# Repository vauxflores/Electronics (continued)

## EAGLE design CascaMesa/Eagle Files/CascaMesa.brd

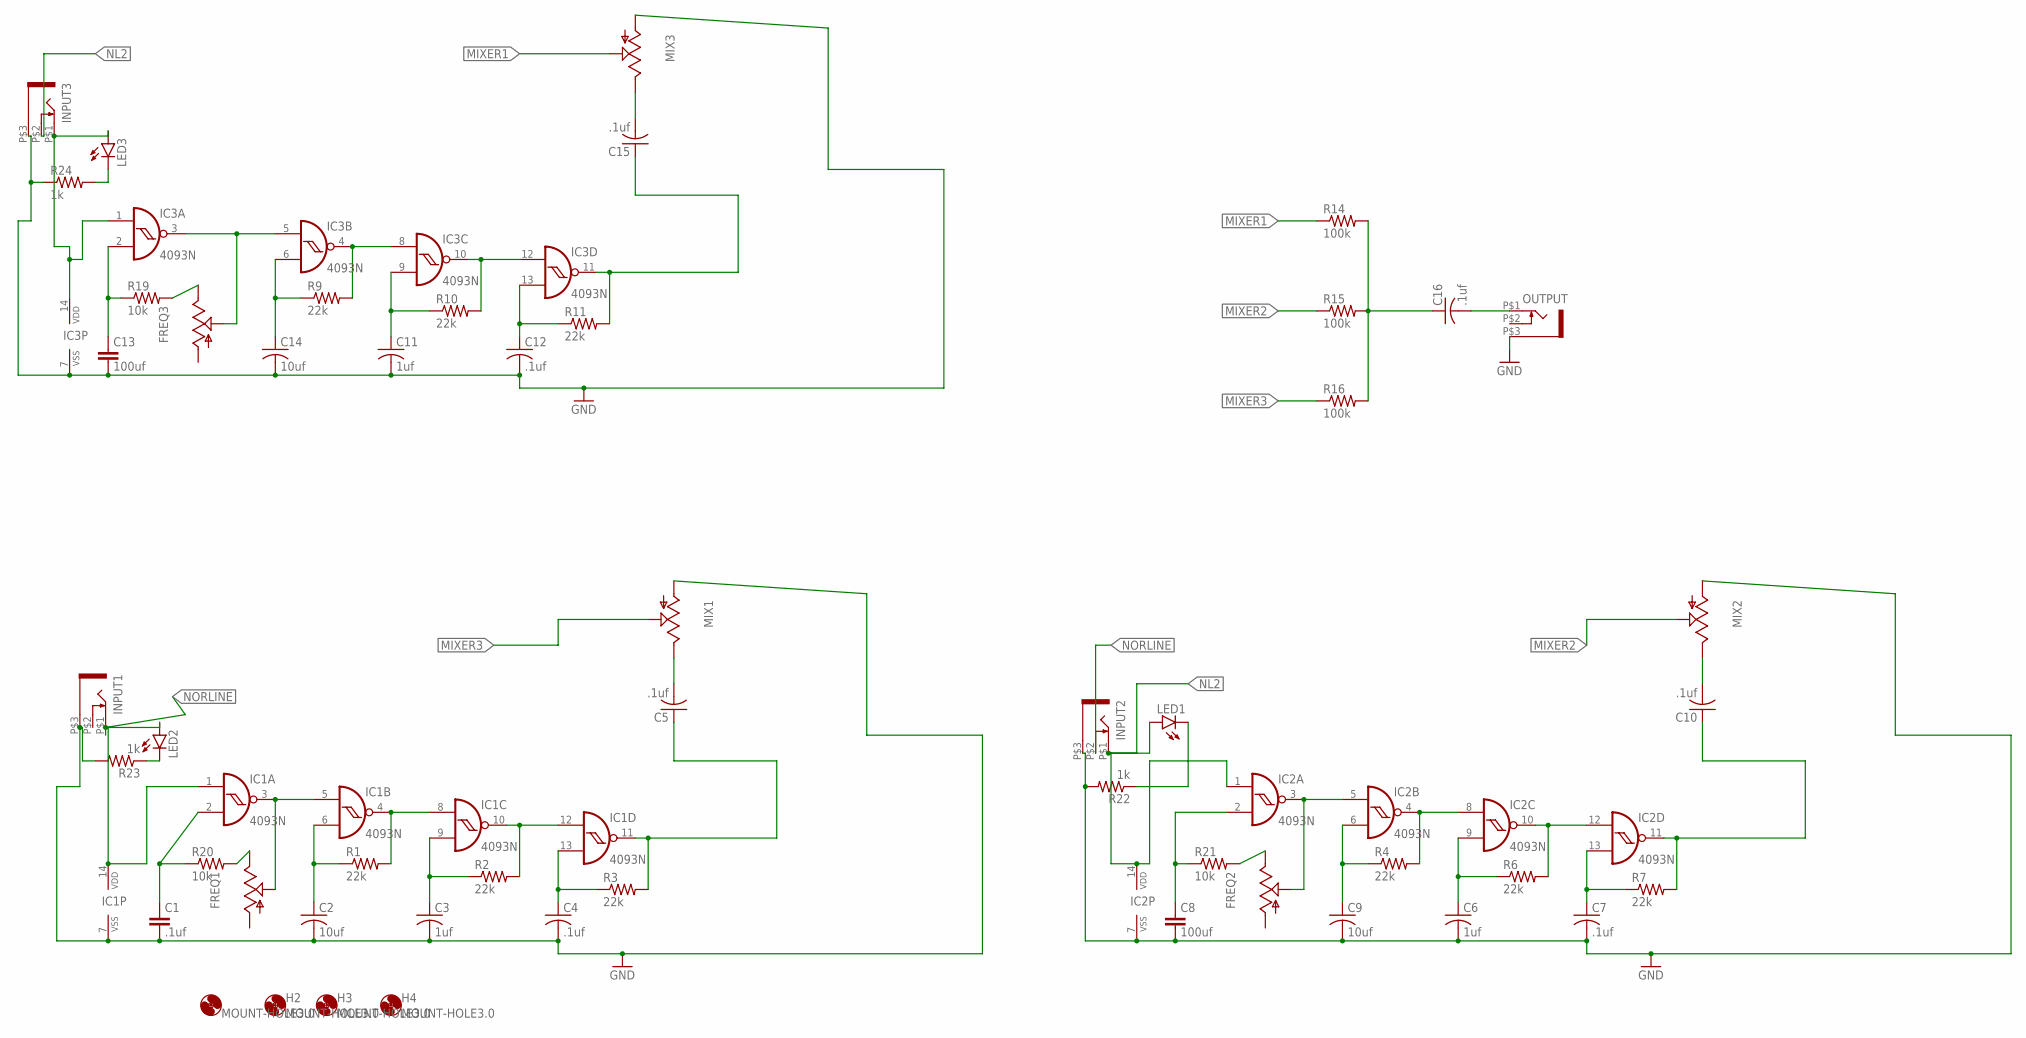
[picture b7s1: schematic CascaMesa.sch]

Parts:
C1, C4, C5, C7, C10, C12, C15, C16: .1uf; C050-025X075
C2, C9, C14: 10uf; C050-025X075
C3, C6, C11: 1uf; C050-025X075
C8, C13: 100uf; C050-025X075
FREQ1, FREQ2, FREQ3: 9MM_SNAP-IN_POT_; 9MM_SNAP-IN_POT
H1, H2, H3, H4: MOUNT-HOLE3.0; 3,0
IC1, IC2, IC3: 4093N; DIL14
INPUT1, INPUT2, INPUT3: WQP-PJ301M-12_JACK
LED1, LED2, LED3: LED3MM
MIX1, MIX2, MIX3: 9MM_SNAP-IN_POT_; 9MM_SNAP-IN_POT
OUTPUT: WQP-PJ301M-12_JACK
R1, R2, R3, R4, R6, R7, R9, R10, R11: 22k; 0207/7
R14, R15, R16: 100k; 0207/7
R19, R20, R21: 10k; 0207/7
R22, R23, R24: 1k; 0207/7

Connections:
GND: C1.2, C2.2, C3.2, C4.2, C6.2, C7.2, C8.2, C9.2, C11.2, C12.2, C13.2, C14.2, IC1.7 (VSS), IC2.7 (VSS), IC3.7 (VSS), INPUT1.P$3 (1), INPUT2.P$3 (1), INPUT3.P$3 (1), MIX1.1 (A), MIX2.1 (A), MIX3.1 (A), OUTPUT.P$3 (1), R22.2, R23.2, R24.1
MIXER1: MIX3.2 (S), R14.1
MIXER2: MIX2.2 (S), R15.1
MIXER3: MIX1.2 (S), R16.1
unnamed: FREQ1.2 (S), IC1.3 (O), IC1.5 (I0)
unnamed: IC1.4 (O), IC1.8 (I0), R1.2
unnamed: IC1.10 (O), IC1.12 (I0), R2.2
unnamed: C1.1, IC1.2 (I1), R20.1
unnamed: C2.1, IC1.6 (I1), R1.1
unnamed: C3.1, IC1.9 (I1), R2.1
unnamed: C4.1, IC1.13 (I1), R3.1
unnamed: C5.2, MIX1.3 (E)
unnamed: C16.1, R14.2, R15.2, R16.2
unnamed: C5.1, IC1.11 (O), R3.2
unnamed: LED1.K (C), R22.1
unnamed: FREQ2.2 (S), IC2.3 (O), IC2.5 (I0)
unnamed: IC2.4 (O), IC2.8 (I0), R4.2
unnamed: IC2.10 (O), IC2.12 (I0), R6.2
unnamed: C8.1, IC2.2 (I1), R21.1
unnamed: C9.1, IC2.6 (I1), R4.1
unnamed: C6.1, IC2.9 (I1), R6.1
unnamed: C7.1, IC2.13 (I1), R7.1
unnamed: C16.2, OUTPUT.P$1 (2)
unnamed: C10.1, IC2.11 (O), R7.2
unnamed: C10.2, MIX2.3 (E)
unnamed: FREQ3.2 (S), IC3.3 (O), IC3.5 (I0)
unnamed: IC3.4 (O), IC3.8 (I0), R9.2
unnamed: IC3.10 (O), IC3.12 (I0), R10.2
unnamed: C13.1, IC3.2 (I1), R19.1
unnamed: C14.1, IC3.6 (I1), R9.1
unnamed: C11.1, IC3.9 (I1), R10.1
unnamed: C12.1, IC3.13 (I1), R11.1
unnamed: LED2.K (C), R23.1
unnamed: FREQ2.3 (E), R21.2
unnamed: C15.1, IC3.11 (O), R11.2
unnamed: C15.2, MIX3.3 (E)
unnamed: FREQ1.3 (E), R20.2
unnamed: IC3.1 (I0), IC3.14 (VDD), INPUT3.P$1 (2), LED3.A
unnamed: LED3.K (C), R24.2
unnamed: FREQ3.3 (E), R19.2
NL2: IC2.1 (I0), IC2.14 (VDD), INPUT2.P$1 (2), INPUT3.P$2 (3), LED1.A
NORLINE: IC1.1 (I0), IC1.14 (VDD), INPUT1.P$1 (2), INPUT2.P$2 (3), LED2.A

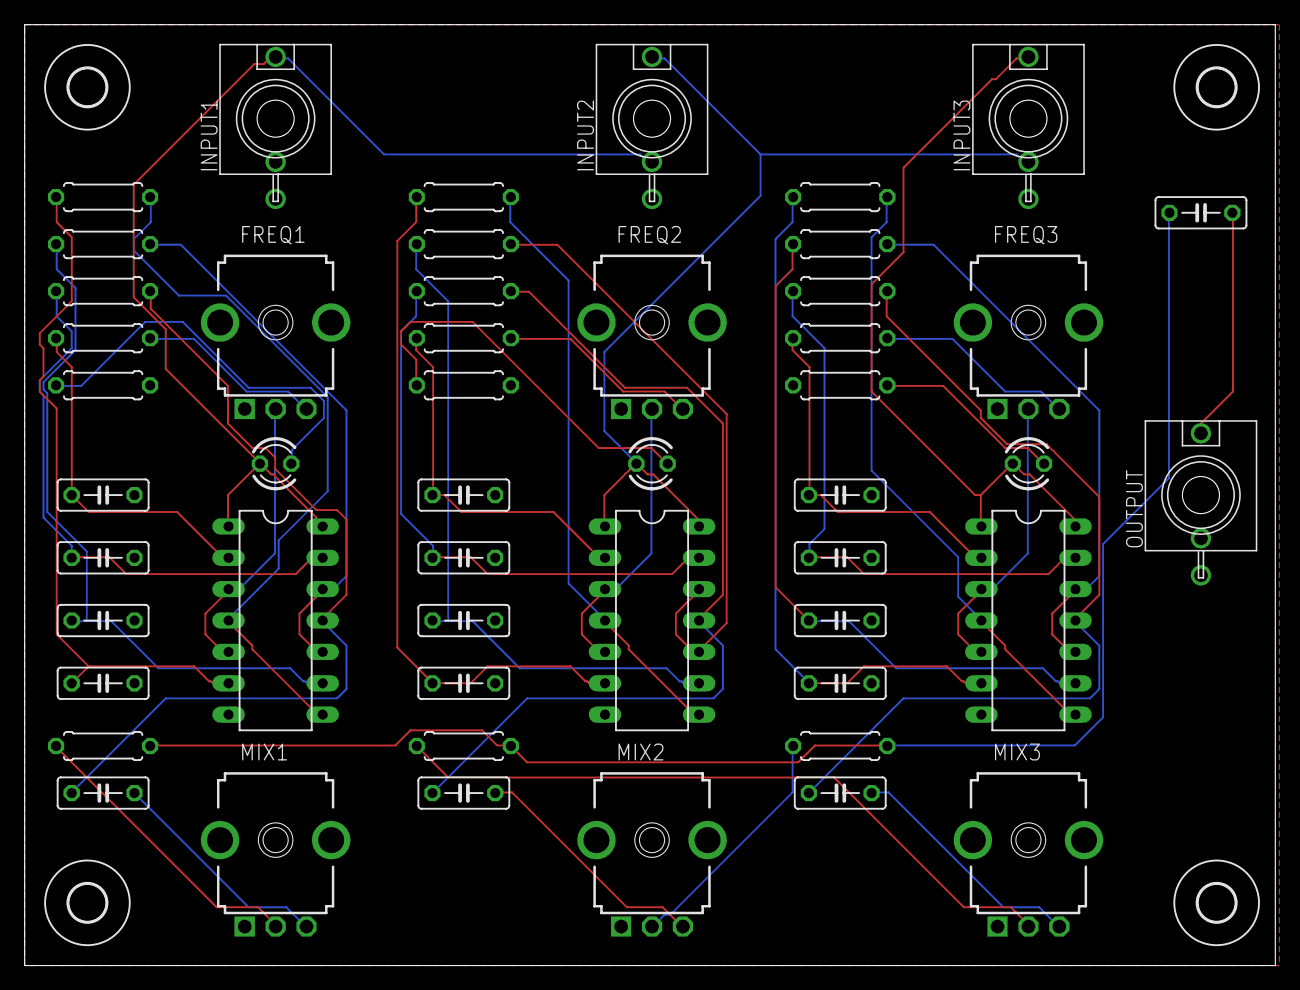
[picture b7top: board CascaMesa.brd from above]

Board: 2 copper layers, 101.3 x 76.2 mm, 54 parts (0 on the bottom side), 42 nets.

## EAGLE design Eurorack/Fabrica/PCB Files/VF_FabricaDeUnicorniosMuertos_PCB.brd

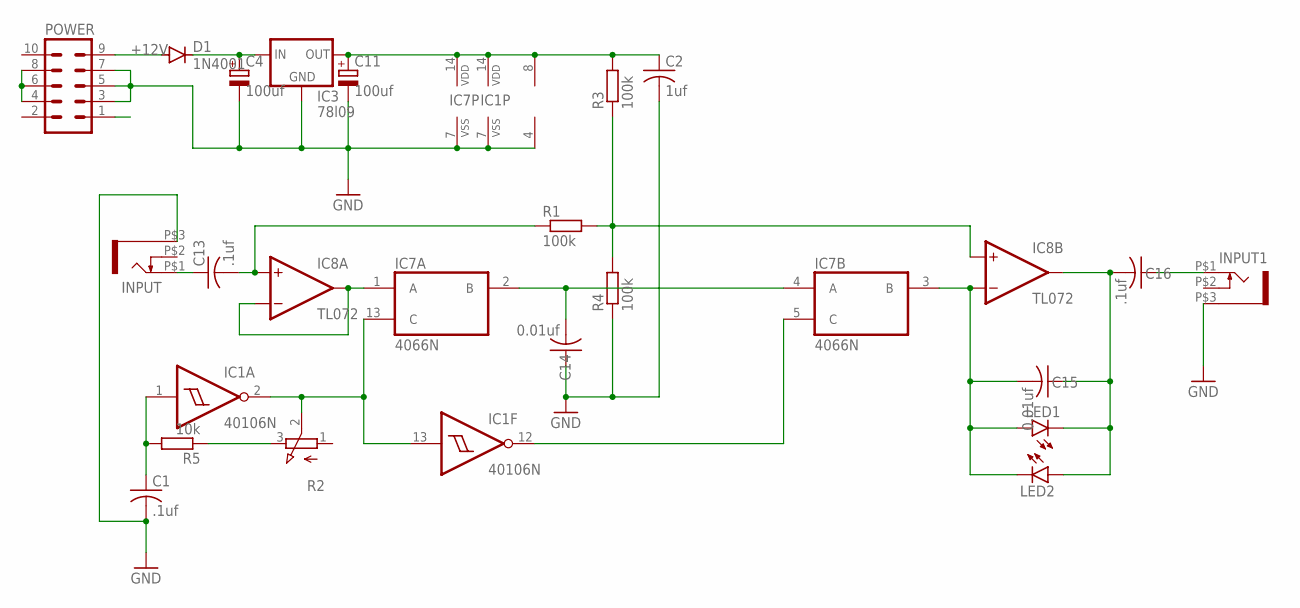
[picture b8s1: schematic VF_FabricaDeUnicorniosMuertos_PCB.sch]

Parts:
C1, C13, C16: .1uf; C050-025X075
C2: 1uf; C050-025X075
C4, C11: 100uf; E2,5-7
C14, C15: 0.01uf; C050-025X075
D1: 1N4001; DO41-10
IC1: 40106N; DIL14
IC3: 78l09; 78LXX
IC7: 4066N; DIL14
IC8: TL072; DIL08
INPUT, INPUT1: WQP-PJ301M-12_JACK
LED1, LED2: LED3MM
POWER: 10_PIN_HEADER; MA05-2
R1, R3, R4: 100k; 7MM_RESISTOR
R2: EVUF2L; EVUFXL
R5: 10k; 7MM_RESISTOR

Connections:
+12V: C4.+, D1.C, IC3.IN
-12V: POWER.1
GND: C1.2, C2.2, C4.-, C11.-, C14.1, IC1.7 (VSS), IC3.GND, IC7.7 (VSS), IC8.4 (V-), INPUT.P$3 (1), INPUT1.P$3 (1), POWER.3, POWER.5, POWER.7, R4.1
GND2: POWER.4, POWER.6, POWER.8
unnamed: C1.1, IC1.1 (I), R5.2
unnamed: C13.1, INPUT.P$1 (2)
unnamed: C16.1, INPUT1.P$1 (2)
unnamed: R2.3 (E), R5.1
unnamed: C15.2, IC7.3 (B), IC8.6 (-IN), LED1.A, LED2.K (C)
unnamed: IC8.5 (+IN), R1.2, R3.1, R4.2
unnamed: IC1.2 (O), IC1.13 (I), IC7.13 (C), R2.2 (S)
unnamed: D1.A, POWER.9
unnamed: C2.1, C11.+, IC1.14 (VDD), IC3.OUT, IC7.14 (VDD), IC8.8 (V+), R3.2
unnamed: C13.2, IC8.3 (+IN), R1.1
unnamed: IC7.1 (A), IC8.1 (OUT), IC8.2 (-IN)
unnamed: C14.2, IC7.2 (B), IC7.4 (A)
unnamed: IC1.12 (O), IC7.5 (C)
unnamed: C15.1, C16.2, IC8.7 (OUT), LED1.K (C), LED2.A

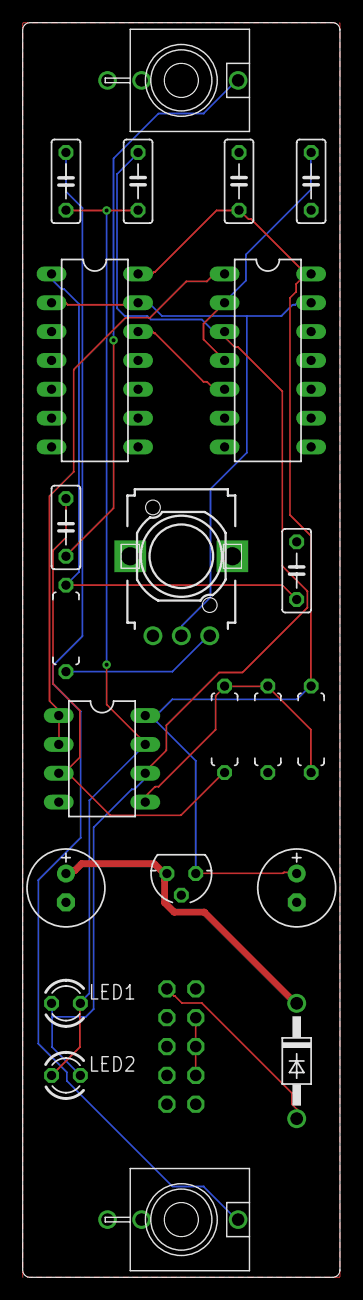
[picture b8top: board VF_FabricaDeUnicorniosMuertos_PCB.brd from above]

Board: 2 copper layers, 27.9 x 110.5 mm, 24 parts (1 on the bottom side), 17 nets.

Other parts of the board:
U$1: EURO_PCB_6HP

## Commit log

2020-05-30 VauxFlores Eyecillator Board and Schematics
2020-05-30 VauxFlores EyeTron Eagle Files
2020-05-30 VauxFlores XimeTron 01_Power Eagle Files
2020-05-30 VauxFlores XimeTron 02_Eyecillator Eagle Files
2020-05-30 VauxFlores XimeTron 09_Gold Standard
2020-05-30 VauxFlores XimeTron 02 Eyecillator Eagle Files
2021-08-24 Create VF_FabricaDeUnicorniosMuertos.zip
    PCB for the VF Fabrica de Unicornios Muertos Switched Capacitor Filter
2021-08-24 Create VF_FabricaDeUnicorniosMuertos_PANEL.zip
    Production Panel for the VF Fabrica de Unicornios Muertos Switched Capacitor Filter
2021-08-24 Create VF_FabricaDeUnicorniosMuertos.zip
    Gerber File for VF's Fabrics Switch Cap Filter
2021-08-24 Create VF_FabricaDeUnicorniosMuertos_PANEL.zip
    Gerber File for VF's Fabrica Switch Cap Filter Production Panel
2021-08-24 Create VF_FabricaDeUnicorniosMuertos_PANEL.brd
    Eagle File for VF's Fabrica Switch Cap Filter
2021-08-24 Create VF_FabricaDeUnicorniosMuertos_PANEL.sch
    Eagle files for CF's Fabrica switch cap filter
2021-08-24 Create VF_FabricaDeUnicorniosMuertos_PCB.brd
    Eagle files for CF's Fabrica switch cap filter
2021-08-24 Create VF_FabricaDeUnicorniosMuertos_PCB.sch
    Eagle files for CF's Fabrica switch cap filter
2021-08-24 Delete VF_FabricaDeUnicorniosMuertos.zip
    File management
2021-08-24 Delete VF_FabricaDeUnicorniosMuertos_PANEL.zip
    File Management
2025-01-19 Remove .DS_Store files from repository
